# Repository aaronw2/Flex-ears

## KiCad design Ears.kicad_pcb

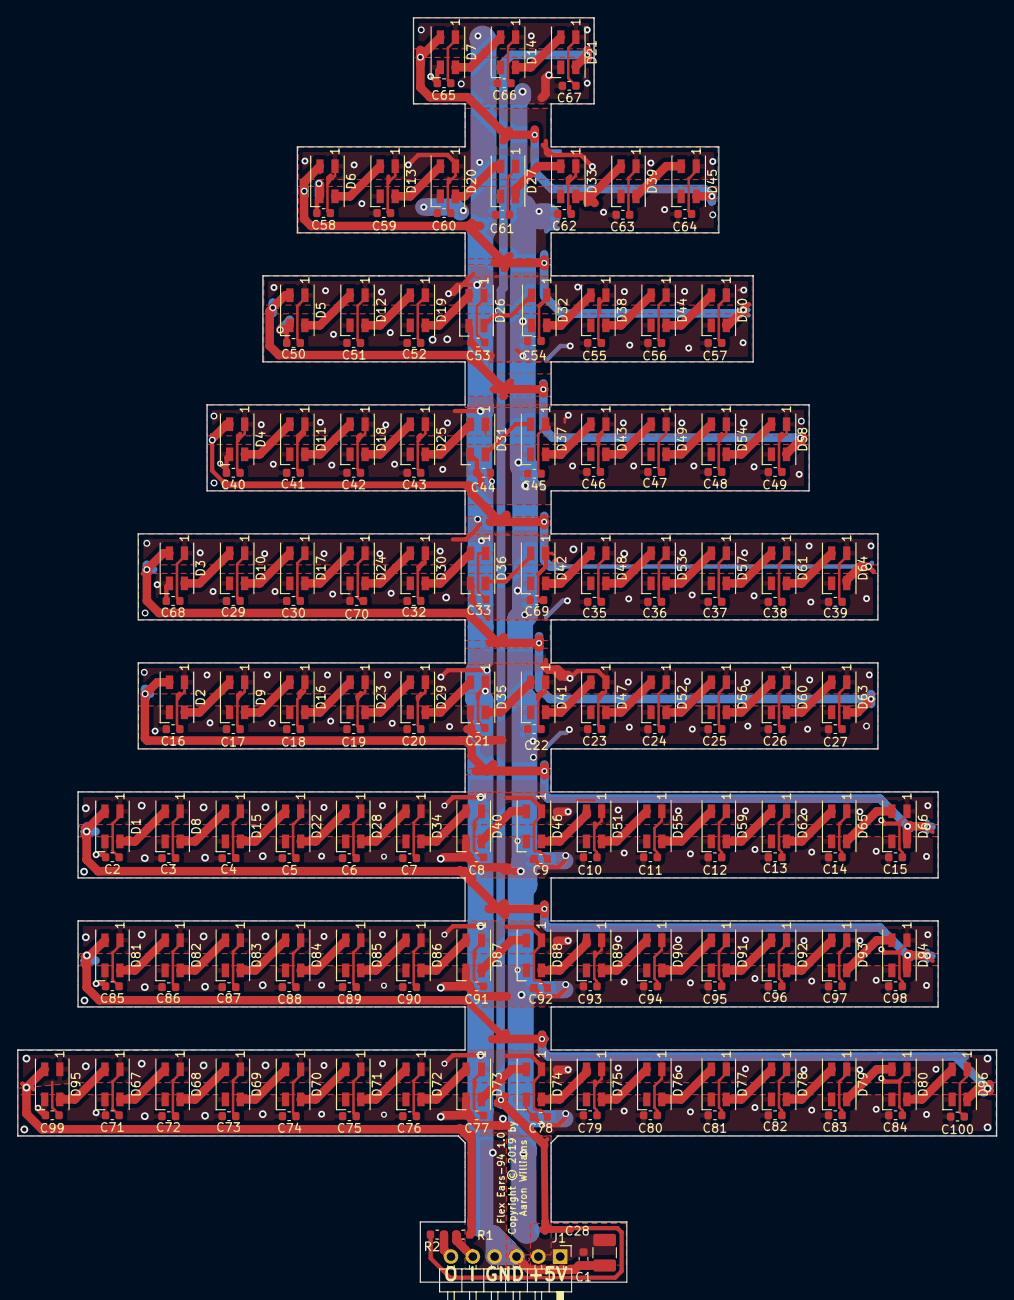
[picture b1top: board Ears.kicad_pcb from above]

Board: 2 copper layers, 113.8 x 147.0 mm, 197 parts (0 on the bottom side), 101 nets.

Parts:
C1, C2, C3, C4, C5, C6, C7, C8, C9, C10, C11, C12, C13, C14, C15, C16, C17, C18, C19, C20, C21, C22, C23, C24, C26, C27, C29, C30, C32, C33, C35, C36, C37, C38, C39, C40, C41, C42, C43, C44, C45, C46, C47, C48, C49, C50, C51, C52, C53, C54, C55, C56, C57, C58, C59, C60, C61, C62, C63, C64, C65, C66, C67, C68, C69, C70, C71, C72, C73, C74, C75, C76, C77, C78, C79, C80, C81, C82, C83, C84, C85, C86, C87, C88, C89, C90, C91, C92, C93, C94, C95, C96, C97, C98, C99, C100: 1uF; C_0603_1608Metric
C25: 10uF; C_0603_1608Metric
C28: 100uF 10V; C_1210_3225Metric_Pad1.42x2.65mm_HandSolder
D1, D2, D3, D4, D5, D6, D7, D8, D9, D10, D11, D12, D13, D14, D15, D16, D17, D18, D19, D20, D21, D22, D23, D24, D25, D26, D27, D28, D29, D30, D31, D32, D33, D34, D35, D36, D37, D38, D39, D40, D41, D42, D43, D44, D45, D46, D47, D48, D49, D50, D51, D52, D53, D54, D55, D56, D57, D58, D59, D60, D61, D62, D63, D64, D65, D66, D67, D68, D69, D70, D71, D72, D73, D74, D75, D76, D77, D78, D79, D80, D81, D82, D83, D84, D85, D86, D87, D88, D89, D90, D91, D92, D93, D94, D95, D96: SK6812; LED_SK6812MINI_PLCC4_3.5x3.5mm_P1.75mm
J1: Conn_01x06_Male; Pin_Header_Angled_1x06_Pitch2.54mm
R1, R2: 22; R_0603_1608Metric

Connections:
/DI: D95.2, R1.1
/DIN: J1.5, R1.2
/DIN_1_2: D81.2, D96.4
/DIN_2_3: D1.2, D94.4
/DIN_3_4: D2.2, D66.4
/DIN_4_5: D3.2, D63.4
/DIN_5_6: D4.2, D64.4
/DIN_6_7: D5.2, D58.4
/DIN_7_8: D6.2, D50.4
/DIN_8_9: D7.2, D45.4
/DO: D21.4, R2.2
/DOUT: J1.6, R2.1
GND: C1.2, C2.2, C3.2, C4.2, C5.2, C6.2, C7.2, C8.2, C9.2, C10.2, C11.2, C12.2, C13.2, C14.2, C15.2, C16.2, C17.2, C18.2, C19.2, C20.2, C21.2, C22.2, C23.2, C24.2, C25.2, C26.2, C27.2, C28.2, C29.2, C30.2, C32.2, C33.2, C35.2, C36.2, C37.2, C38.2, C39.2, C40.2, C41.2, C42.2, C43.2, C44.2, C45.2, C46.2, C47.2, C48.2, C49.2, C50.2, C51.2, C52.2, C53.2, C54.2, C55.2, C56.2, C57.2, C58.2, C59.2, C60.2, C61.2, C62.2, C63.2, C64.2, C65.2, C66.2, C67.2, C68.2, C69.2, C70.2, C71.2, C72.2, C73.2, C74.2, C75.2, C76.2, C77.2, C78.2, C79.2, C80.2, C81.2, C82.2, C83.2, C84.2, C85.2, C86.2, C87.2, C88.2, C89.2, C90.2, C91.2, C92.2, C93.2, C94.2, C95.2, C96.2, C97.2, C98.2, C99.2, C100.2, D1.1, D2.1, D3.1, D4.1, D5.1, D6.1, D7.1, D8.1, D9.1, D10.1, D11.1, D12.1, D13.1, D14.1, D15.1, D16.1, D17.1, D18.1, D19.1, D20.1, D21.1, D22.1, D23.1, D24.1, D25.1, D26.1, D27.1, D28.1, D29.1, D30.1, D31.1, D32.1, D33.1, D34.1, D35.1, D36.1, D37.1, D38.1, D39.1, D40.1, D41.1, D42.1, D43.1, D44.1, D45.1, D46.1, D47.1, D48.1, D49.1, D50.1, D51.1, D52.1, D53.1, D54.1, D55.1, D56.1, D57.1, D58.1, D59.1, D60.1, D61.1, D62.1, D63.1, D64.1, D65.1, D66.1, D67.1, D68.1, D69.1, D70.1, D71.1, D72.1, D73.1, D74.1, D75.1, D76.1, D77.1, D78.1, D79.1, D80.1, D81.1, D82.1, D83.1, D84.1, D85.1, D86.1, D87.1, D88.1, D89.1, D90.1, D91.1, D92.1, D93.1, D94.1, D95.1, D96.1, J1.3, J1.4
unnamed: D1.4, D8.2
unnamed: D2.4, D9.2
unnamed: D3.4, D10.2
unnamed: D10.4, D17.2
unnamed: D4.4, D11.2
unnamed: D11.4, D18.2
unnamed: D5.4, D12.2
unnamed: D12.4, D19.2
unnamed: D6.4, D13.2
unnamed: D13.4, D20.2
unnamed: D7.4, D14.2
unnamed: D14.4, D21.2
unnamed: D8.4, D15.2
unnamed: D15.4, D22.2
unnamed: D9.4, D16.2
unnamed: D16.4, D23.2
unnamed: D17.4, D24.2
unnamed: D18.4, D25.2
unnamed: D19.4, D26.2
unnamed: D20.4, D27.2
unnamed: D22.4, D28.2
unnamed: D23.4, D29.2
unnamed: D24.4, D30.2
unnamed: D25.4, D31.2
unnamed: D26.4, D32.2
unnamed: D27.4, D33.2
unnamed: D28.4, D34.2
unnamed: D29.4, D35.2
unnamed: D30.4, D36.2
unnamed: D31.4, D37.2
unnamed: D32.4, D38.2
unnamed: D33.4, D39.2
unnamed: D34.4, D40.2
unnamed: D35.4, D41.2
unnamed: D36.4, D42.2
unnamed: D37.4, D43.2
unnamed: D38.4, D44.2
unnamed: D39.4, D45.2
unnamed: D40.4, D46.2
unnamed: D41.4, D47.2
unnamed: D42.4, D48.2
unnamed: D43.4, D49.2
unnamed: D44.4, D50.2
unnamed: D46.4, D51.2
unnamed: D47.4, D52.2
unnamed: D48.4, D53.2
unnamed: D49.4, D54.2
unnamed: D51.4, D55.2
unnamed: D52.4, D56.2
unnamed: D53.4, D57.2
unnamed: D54.4, D58.2
unnamed: D55.4, D59.2
unnamed: D56.4, D60.2
unnamed: D57.4, D61.2
unnamed: D59.4, D62.2
unnamed: D60.4, D63.2
unnamed: D61.4, D64.2
unnamed: D62.4, D65.2
unnamed: D65.4, D66.2
unnamed: D67.2, D95.4
unnamed: D67.4, D68.2
unnamed: D68.4, D69.2
unnamed: D69.4, D70.2
unnamed: D70.4, D71.2
unnamed: D71.4, D72.2
unnamed: D72.4, D73.2
unnamed: D73.4, D74.2
unnamed: D74.4, D75.2
unnamed: D75.4, D76.2
unnamed: D76.4, D77.2
unnamed: D77.4, D78.2
unnamed: D78.4, D79.2
unnamed: D79.4, D80.2
unnamed: D80.4, D96.2
unnamed: D81.4, D82.2
unnamed: D82.4, D83.2
unnamed: D83.4, D84.2
unnamed: D84.4, D85.2
unnamed: D85.4, D86.2
unnamed: D86.4, D87.2
unnamed: D87.4, D88.2
unnamed: D88.4, D89.2
unnamed: D89.4, D90.2
unnamed: D90.4, D91.2
unnamed: D91.4, D92.2
unnamed: D92.4, D93.2
unnamed: D93.4, D94.2
VCC: C1.1, C2.1, C3.1, C4.1, C5.1, C6.1, C7.1, C8.1, C9.1, C10.1, C11.1, C12.1, C13.1, C14.1, C15.1, C16.1, C17.1, C18.1, C19.1, C20.1, C21.1, C22.1, C23.1, C24.1, C25.1, C26.1, C27.1, C28.1, C29.1, C30.1, C32.1, C33.1, C35.1, C36.1, C37.1, C38.1, C39.1, C40.1, C41.1, C42.1, C43.1, C44.1, C45.1, C46.1, C47.1, C48.1, C49.1, C50.1, C51.1, C52.1, C53.1, C54.1, C55.1, C56.1, C57.1, C58.1, C59.1, C60.1, C61.1, C62.1, C63.1, C64.1, C65.1, C66.1, C67.1, C68.1, C69.1, C70.1, C71.1, C72.1, C73.1, C74.1, C75.1, C76.1, C77.1, C78.1, C79.1, C80.1, C81.1, C82.1, C83.1, C84.1, C85.1, C86.1, C87.1, C88.1, C89.1, C90.1, C91.1, C92.1, C93.1, C94.1, C95.1, C96.1, C97.1, C98.1, C99.1, C100.1, D1.3, D2.3, D3.3, D4.3, D5.3, D6.3, D7.3, D8.3, D9.3, D10.3, D11.3, D12.3, D13.3, D14.3, D15.3, D16.3, D17.3, D18.3, D19.3, D20.3, D21.3, D22.3, D23.3, D24.3, D25.3, D26.3, D27.3, D28.3, D29.3, D30.3, D31.3, D32.3, D33.3, D34.3, D35.3, D36.3, D37.3, D38.3, D39.3, D40.3, D41.3, D42.3, D43.3, D44.3, D45.3, D46.3, D47.3, D48.3, D49.3, D50.3, D51.3, D52.3, D53.3, D54.3, D55.3, D56.3, D57.3, D58.3, D59.3, D60.3, D61.3, D62.3, D63.3, D64.3, D65.3, D66.3, D67.3, D68.3, D69.3, D70.3, D71.3, D72.3, D73.3, D74.3, D75.3, D76.3, D77.3, D78.3, D79.3, D80.3, D81.3, D82.3, D83.3, D84.3, D85.3, D86.3, D87.3, D88.3, D89.3, D90.3, D91.3, D92.3, D93.3, D94.3, D95.3, D96.3, J1.1, J1.2

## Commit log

2018-09-21 Initial checkin
2019-02-05 Added more LEDs and board cleanup
2019-02-05 Updated rigid areas.
2019-02-05 Fixed fill region not assigned to the proper net.
2019-02-05 Fixed fill area and added back silkscreen
2019-02-05 timestamp
2019-05-15 Ears sent to production.
    Note that the sk6812mini footprints are broken for reflow.
    Don't use this. I had to hand resolder every single LED,
    often multiple times.

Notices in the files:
Ears.kicad_pcb:
Flex Ear LEDs Copyright © 2019 by Aaron Williams
